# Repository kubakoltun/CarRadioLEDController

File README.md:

AtTiny85 documentation:
https://ww1.microchip.com/downloads/aemDocuments/documents/OTH/ProductDocuments/DataSheets/Atmel-2586-AVR-8-bit-Microcontroller-ATtiny25-ATtiny45-ATtiny85_Datasheet.pdf

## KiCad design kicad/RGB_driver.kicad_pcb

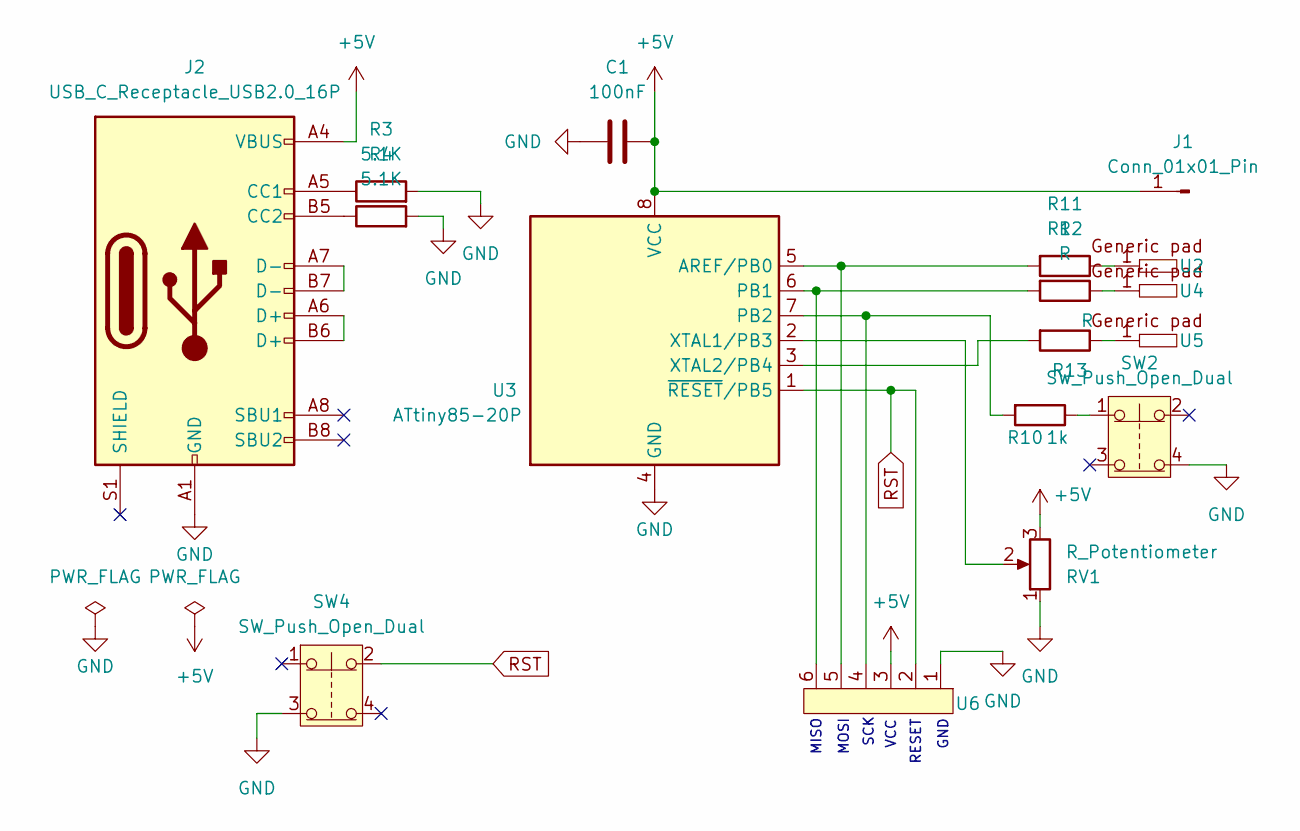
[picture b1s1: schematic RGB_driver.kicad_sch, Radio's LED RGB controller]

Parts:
C1: 100nF; C_Disc_D7.0mm_W2.5mm_P5.00mm
J1: Conn_01x01_Pin; simple_generic_pad
J2: USB_C_Receptacle_USB2.0_16P; USB_C_Receptacle_GCT_USB4105-xx-A_16P_TopMnt_Horizontal
R3, R4: 5.1K; resistor_footprint
R10: 1k; resistor_footprint
R11, R12, R13: R; resistor_footprint
RV1: R_Potentiometer; potentiometer_custom
SW2, SW4: SW_Push_Open_Dual; a_huge_button
U2, U4, U5: simple_generic_pad
U3: ATtiny85-20P; DIP-8_W7.62mm
U6: SPI

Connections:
+5V: C1.1, J1.1, J2.A4 (VBUS), J2.A9 (VBUS), J2.B4 (VBUS), J2.B9 (VBUS), RV1.3, U3.8 (VCC), U6.3
GND: C1.2, J2.A1 (GND), J2.A12 (GND), J2.B1 (GND), J2.B12 (GND), R3.2, R4.2, RV1.1, SW2.4, SW4.3, U3.4 (GND), U6.1
unnamed: J2.A5 (CC1), R3.1
unnamed: J2.B5 (CC2), R4.1
unnamed: J2.A6 (D+), J2.B6 (D+)
unnamed: J2.A7 (D-), J2.B7 (D-)
unnamed: R10.1, SW2.1
unnamed: R11.1, U2.1
unnamed: R12.1, U4.1
unnamed: R13.1, U5.1
unnamed: R11.2, U3.5 (AREF/PB0), U6.5
unnamed: R12.2, U3.6 (PB1), U6.6
unnamed: R10.2, U3.7 (PB2), U6.4
unnamed: RV1.2, U3.2 (XTAL1/PB3)
unnamed: R13.2, U3.3 (XTAL2/PB4)
RST: SW4.2, U3.1 (~RESET/PB5), U6.2

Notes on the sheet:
SCK
GND
VCC
MISO
RESET
MOSI

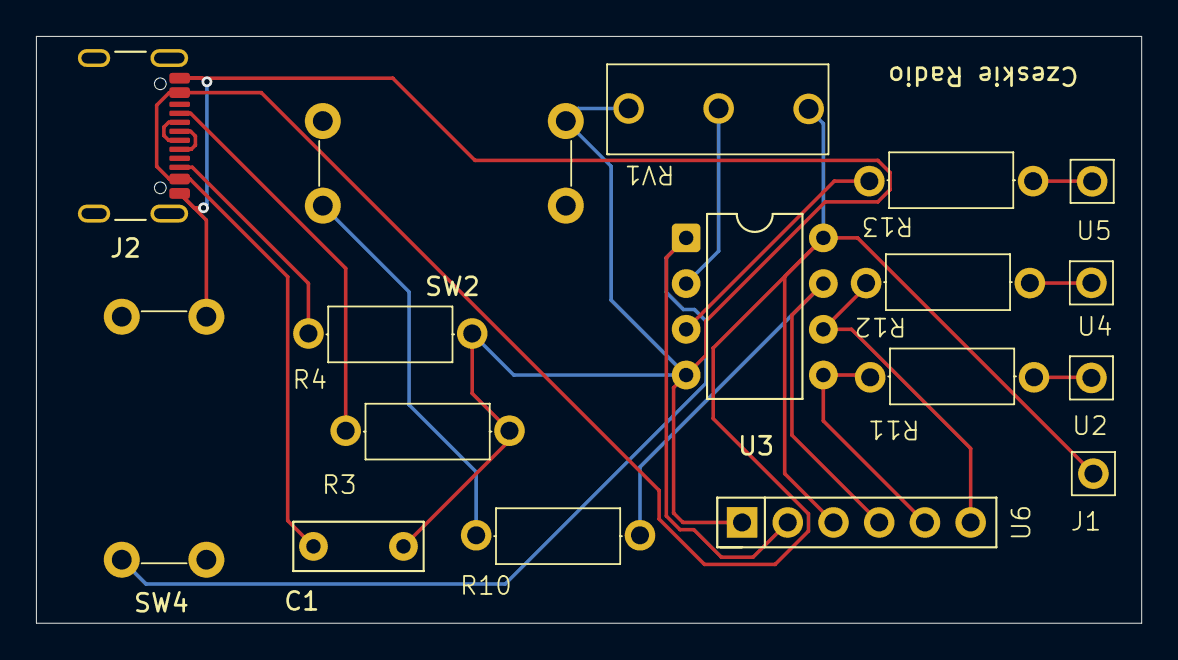
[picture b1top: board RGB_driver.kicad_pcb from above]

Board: 2 copper layers, 61.4 x 32.6 mm, 17 parts (0 on the bottom side), 16 nets.

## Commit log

2025-12-29 feat: init - simple code to change colors with a button and change the brightness with a potentiometer, kicad schemas of the controller
2025-12-29 change: deleted the attiny85 documentation
2026-01-09 change: finished footprints layers, updated pcb with footprints - wip
2026-01-10 change: added footprints - button, potentiometer, fixed and connected pcb
2026-01-11 change: corrected button size, reorganized pcb
2026-01-11 change: plotted gerber fiels
2026-02-05 change: referenced pins from attiny
2026-02-07 fix: reset, spi, main button and potentiometer changed pins and connections, no capacitor on reset, ceramic capacitor at vcc
2026-02-08 fix: power supply for reset removed, new gerber files
2026-02-09 change: external power pad changed to a passive connector, new gerber files
2026-02-09 change: ignoring backups of the kicad project
